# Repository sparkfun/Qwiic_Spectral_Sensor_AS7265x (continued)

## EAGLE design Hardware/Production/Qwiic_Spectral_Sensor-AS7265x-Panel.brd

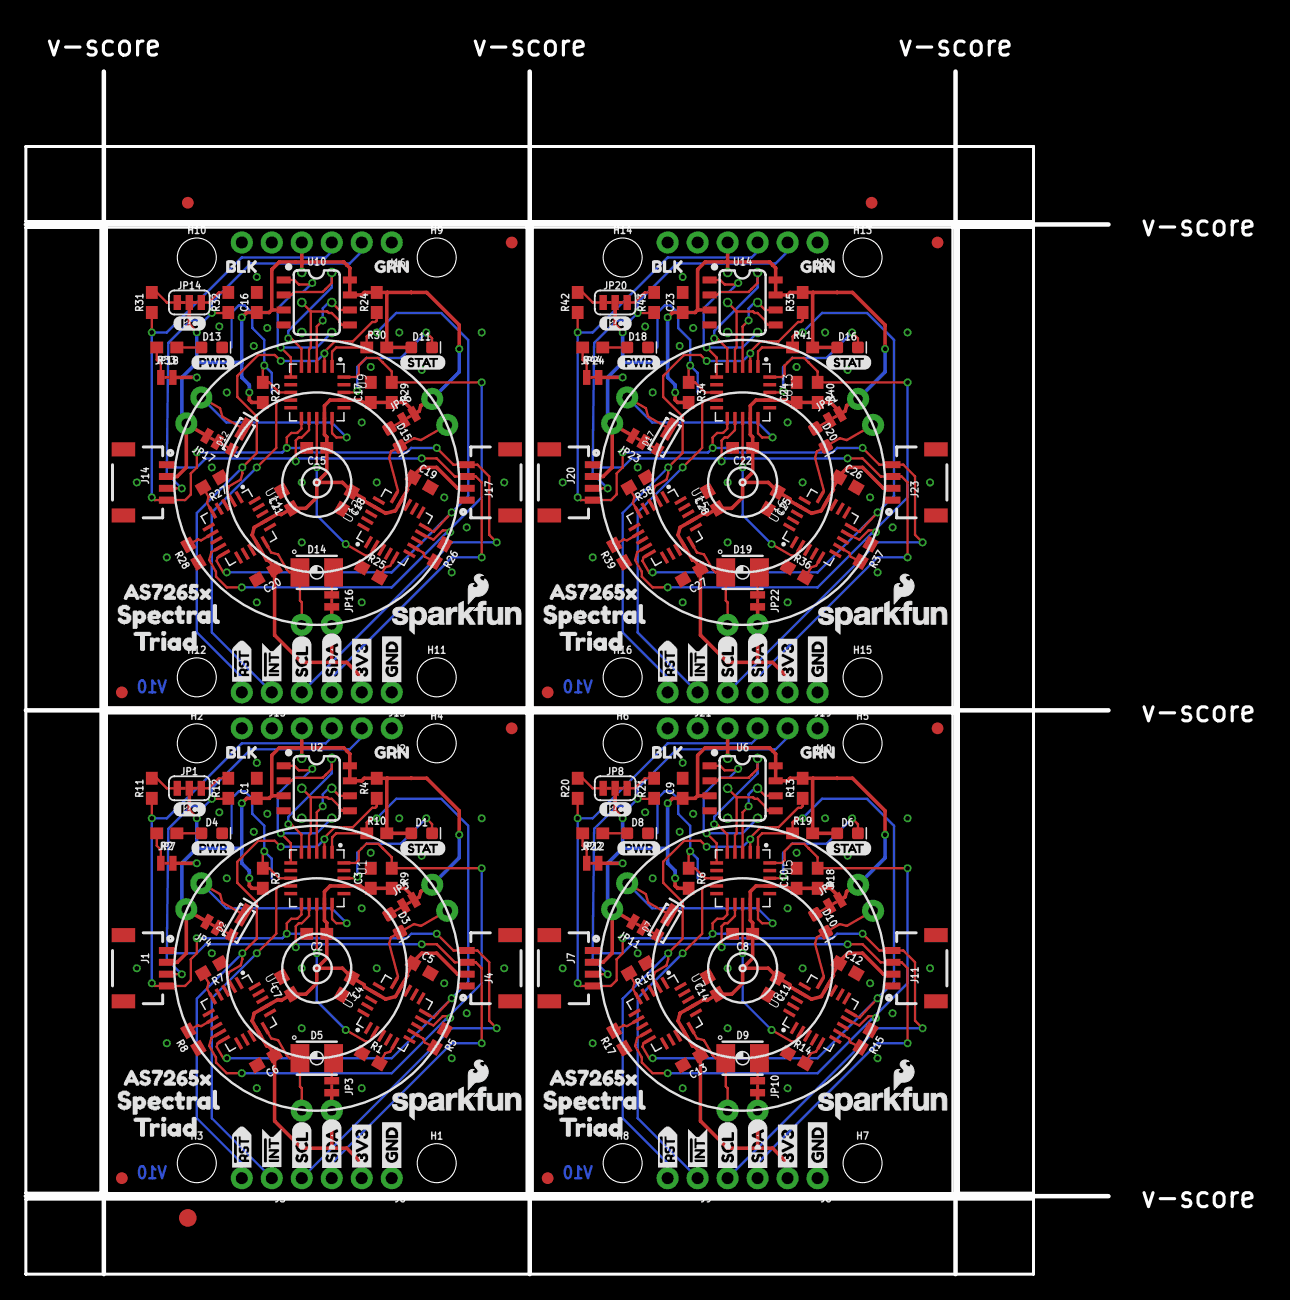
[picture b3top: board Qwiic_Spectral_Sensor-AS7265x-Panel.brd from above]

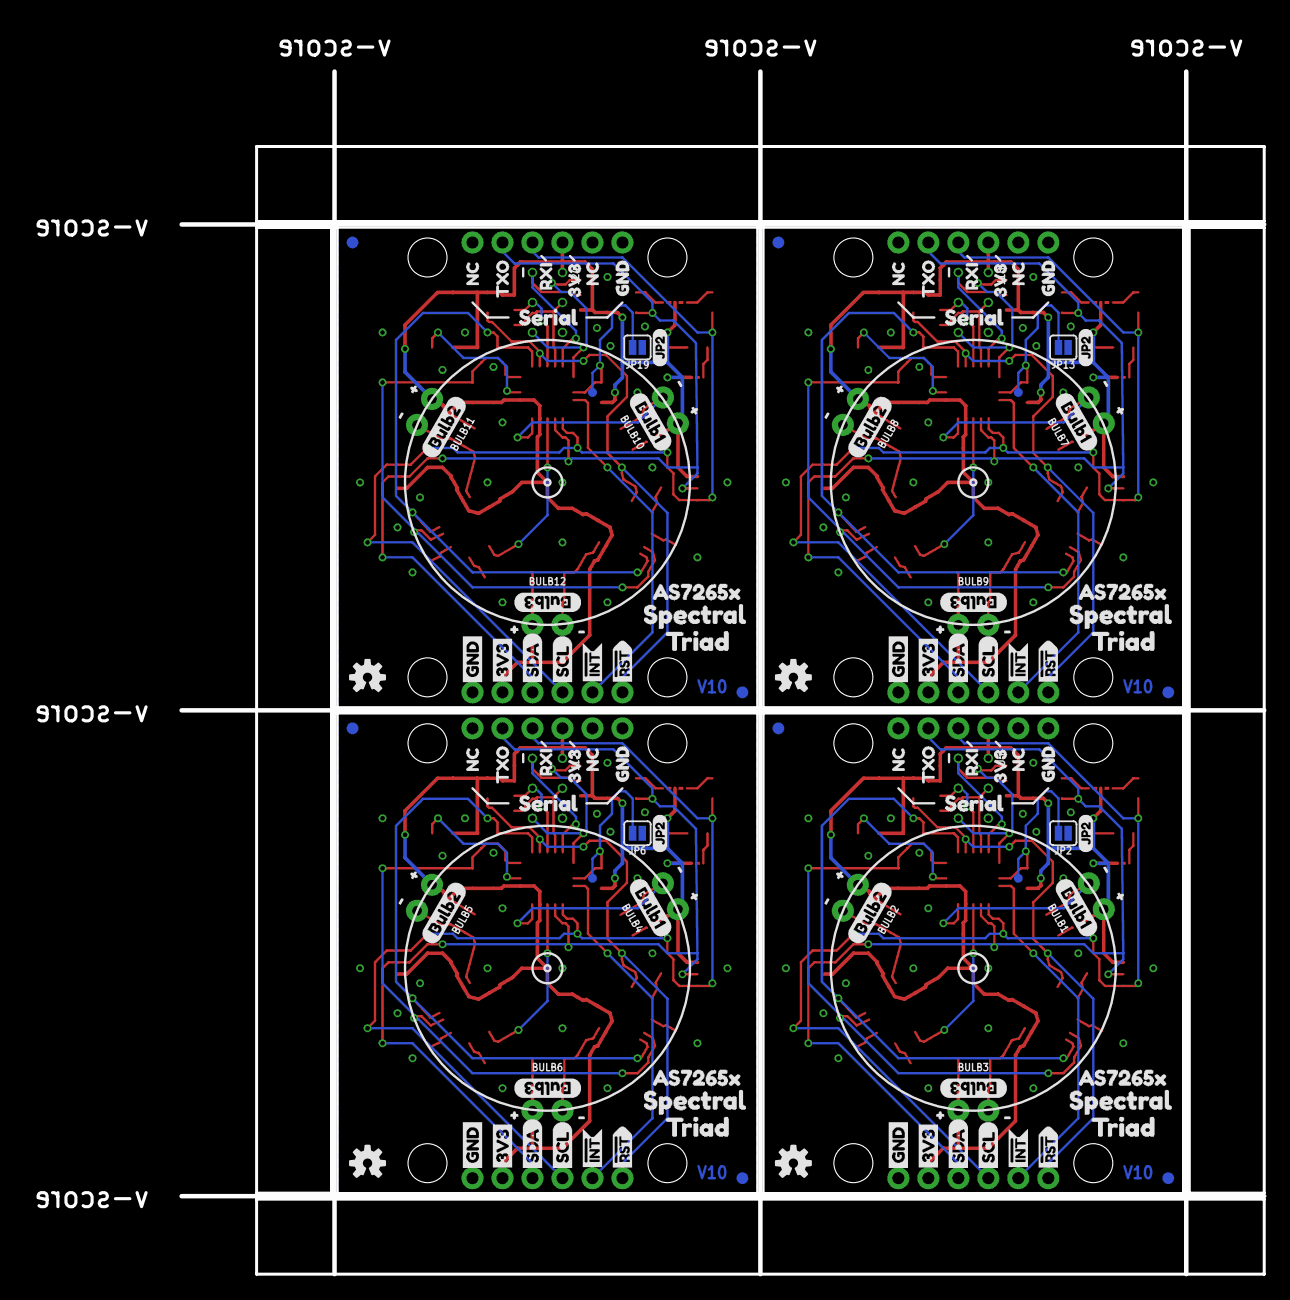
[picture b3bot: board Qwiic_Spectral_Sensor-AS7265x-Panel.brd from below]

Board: 2 copper layers, 104.9 x 105.7 mm, 375 parts (140 on the bottom side), 116 nets.

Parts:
BULB1, BULB2, BULB3, BULB4, BULB5, BULB6, BULB7, BULB8, BULB9, BULB10, BULB11, BULB12: LED_5MM_NOSILK
C1, C9, C16, C23: 1.0uF; 0603
C2, C4, C6, C8, C11, C13, C15, C18, C20, C22, C25, C27: 0.1uF; 0603
C3, C5, C7, C10, C12, C14, C17, C19, C21, C24, C26, C28: 10uF; 0603
D1, D6, D11, D16: BLUE; LED-0603
D2, D7, D12, D17: 5700k; SUPER_BRIGHT_SMD_LED_3014
D3, D10, D15, D20: IR; LED-0603
D4, D8, D13, D18: RED; LED-0603
D5, D9, D14, D19: UV; PLCC-2
E$1, E$2: FIDUCIAL-1X2
E$3: FIDUCIAL-1.5X3
FD1, FD2, FD3, FD4, FD5, FD6, FD7, FD8, FD9, FD10, FD11, FD12, FD13, FD14, FD15, FD16: FIDUCIAL1X2; FIDUCIAL-1X2
H1, H2, H3, H4, H5, H6, H7, H8, H9, H10, H11, H12, H13, H14, H15, H16: STAND-OFF
J1, J4, J7, J11, J14, J17, J20, J23: 1X04_1MM_RA
J2, J10, J16, J22: Serial Interface; 1X06_NO_SILK
J3, J9, J15, J21: 1X02_NO_SILK
J5, J12, J18, J24: Flash Programming; 2X3_TEST_POINTS
J6, J8, J13, J19: PTH; 1X04_NO_SILK
JP1, JP8, JP14, JP20: SMT-JUMPER_3_2-NC_TRACE_SILK
JP2, JP6, JP13, JP19: SMT-JUMPER_2_NO_SILK
JP3, JP4, JP5, JP7, JP9, JP10, JP11, JP12, JP15, JP16, JP17, JP18, JP21, JP22, JP23, JP24: SMT-JUMPER_2_NC_TRACE_NO-SILK
LOGO1, LOGO3, LOGO6, LOGO8: SFE_LOGO_NAME_FLAME.1_INCH; SFE_LOGO_NAME_FLAME_.1
LOGO2, LOGO4, LOGO5, LOGO7: OSHW-LOGOS; OSHW-LOGO-S
R1, R3, R4, R5, R6, R7, R8, R13, R14, R15, R16, R17, R23, R24, R25, R26, R27, R28, R34, R35, R36, R37, R38, R39: 10k; 0603
R2, R22, R33, R44: 1k; 0603
R9, R10, R11, R12, R18, R19, R20, R21, R29, R30, R31, R32, R40, R41, R42, R43: 2.2k; 0603
TP1, TP2, TP3, TP4: PAD.03X.03
U1, U5, U9, U13: AS72651; LGA20
U2, U6, U10, U14: 4MB Flash; SO08
U3, U8, U12, U16: AS72652; LGA20
U4, U7, U11, U15: AS72653; LGA20
U$1, U$36, U$37, U$75, U$76, U$77, U$115, U$116, U$117, U$155, U$156, U$157: #0
U$2, U$41, U$81, U$121: I_SUPER2_C-()-03
U$3, U$42, U$82, U$122: PWR-()-03
U$4, U$14, U$43, U$52, U$83, U$92, U$123, U$132: AS7265X0
U$5, U$44, U$84, U$124: BULB15
U$6, U$45, U$85, U$125: BULB26
U$7, U$46, U$86, U$126: BULB37
U$8, U$62, U$102, U$142: JP20
U$9, U$13, U$47, U$51, U$87, U$91, U$127, U$131: SPECTRAL1
U$10, U$48, U$88, U$128: STAT4
U$11, U$12, U$49, U$50, U$89, U$90, U$129, U$130: TRIAD2
U$15, U$53, U$93, U$133: 3V33
U$16, U$54, U$94, U$134: BLK7
U$17, U$55, U$95, U$135: GND5
U$18, U$56, U$96, U$136: GRN6
U$19, U$20, U$57, U$58, U$97, U$98, U$137, U$138: NC4
U$21, U$59, U$99, U$139: RXI2
U$22, U$60, U$100, U$140: SERIAL0
U$23, U$61, U$101, U$141: TXO1
U$24, U$31, U$63, U$70, U$103, U$110, U$143, U$150: 3V3-04
U$25, U$30, U$64, U$69, U$104, U$109, U$144, U$149: GND-04
U$26, U$32, U$65, U$71, U$105, U$111, U$145, U$151: SDA-[)
U$27, U$33, U$66, U$72, U$106, U$112, U$146, U$152: SCL-[)
U$28, U$34, U$67, U$73, U$107, U$113, U$147, U$153: INT#-[<-04
U$29, U$35, U$68, U$74, U$108, U$114, U$148, U$154: RST#-[>-04
U$38, U$39, U$40, U$78, U$79, U$80, U$118, U$119, U$120, U$158, U$159, U$160: #1

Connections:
3.3V: BULB1.A, BULB2.A, BULB3.A, C1.1, C2.1, C3.1, C4.1, C5.1, C6.1, C7.1, D1.A, J1.2, J2.4, J4.2, J5.2, J8.2, JP1.2, JP3.2, JP4.2, JP5.2, JP7.2, R3.2, R4.2, R9.2, R10.2, U1.14, U1.17, U2.3, U2.7, U2.8, U3.14, U3.17, U4.14, U4.17
3.3V1: BULB4.A, BULB5.A, BULB6.A, C8.1, C9.1, C10.1, C11.1, C12.1, C13.1, C14.1, D6.A, J6.2, J7.2, J10.4, J11.2, J12.2, JP8.2, JP9.2, JP10.2, JP11.2, JP12.2, R6.2, R13.2, R18.2, R19.2, U5.14, U5.17, U6.3, U6.7, U6.8, U7.14, U7.17, U8.14, U8.17
3.3V2: BULB7.A, BULB8.A, BULB9.A, C15.1, C16.1, C17.1, C18.1, C19.1, C20.1, C21.1, D11.A, J13.2, J14.2, J16.4, J17.2, J18.2, JP14.2, JP15.2, JP16.2, JP17.2, JP18.2, R23.2, R24.2, R29.2, R30.2, U9.14, U9.17, U10.3, U10.7, U10.8, U11.14, U11.17, U12.14, U12.17
3.3V3: BULB10.A, BULB11.A, BULB12.A, C22.1, C23.1, C24.1, C25.1, C26.1, C27.1, C28.1, D16.A, J19.2, J20.2, J22.4, J23.2, J24.2, JP20.2, JP21.2, JP22.2, JP23.2, JP24.2, R34.2, R35.2, R40.2, R41.2, U13.14, U13.17, U14.3, U14.7, U14.8, U15.14, U15.17, U16.14, U16.17
!CS_EE: J5.5, U1.6, U2.1
!CS_EE1: J12.5, U5.6, U6.1
!CS_EE2: J18.5, U9.6, U10.1
!CS_EE3: J24.5, U13.6, U14.1
!INT: J3.1, U1.9
!INT1: J9.1, U5.9
!INT2: J15.1, U9.9
!INT3: J21.1, U13.9
!RST: J3.2, R4.1, U1.2, U4.2
!RST1: J9.2, R13.1, U5.2, U7.2
!RST2: J15.2, R24.1, U9.2, U11.2
!RST3: J21.2, R35.1, U13.2, U15.2
!RST-ADDR: U1.13, U3.2
!RST-ADDR1: U5.13, U8.2
!RST-ADDR2: U9.13, U12.2
!RST-ADDR3: U13.13, U16.2
GND: C1.2, C2.2, C3.2, C4.2, C5.2, C6.2, C7.2, D4.C, J1.1, J2.6, J4.1, J5.6, J8.1, JP2.1, R1.1, R5.1, R7.1, R8.1, U1.16, U2.4, U3.16, U4.16
GND1: C8.2, C9.2, C10.2, C11.2, C12.2, C13.2, C14.2, D8.C, J6.1, J7.1, J10.6, J11.1, J12.6, JP6.1, R14.1, R15.1, R16.1, R17.1, U5.16, U6.4, U7.16, U8.16
GND2: C15.2, C16.2, C17.2, C18.2, C19.2, C20.2, C21.2, D13.C, J13.1, J14.1, J16.6, J17.1, J18.6, JP13.1, R25.1, R26.1, R27.1, R28.1, U9.16, U10.4, U11.16, U12.16
GND3: C22.2, C23.2, C24.2, C25.2, C26.2, C27.2, C28.2, D18.C, J19.1, J20.1, J22.6, J23.1, J24.6, JP19.1, R36.1, R37.1, R38.1, R39.1, U13.16, U14.4, U15.16, U16.16
I2C_ENB: JP2.2, R3.1, TP1.P$1, U1.8
I2C_ENB1: JP6.2, R6.1, TP2.P$1, U5.8
I2C_ENB2: JP13.2, R23.1, TP3.P$1, U9.8
I2C_ENB3: JP19.2, R34.1, TP4.P$1, U13.8
LED_DRV: BULB1.K, D2.C, U1.15
LED_DRV1: BULB2.K, D3.C, U3.15
LED_DRV2: BULB3.K, D5.C, U4.15
LED_DRV3: BULB4.K, D7.C, U5.15
LED_DRV4: BULB5.K, D10.C, U8.15
LED_DRV5: BULB6.K, D9.C, U7.15
LED_DRV6: BULB7.K, D12.C, U9.15
LED_DRV7: BULB8.K, D15.C, U12.15
LED_DRV8: BULB9.K, D14.C, U11.15
LED_DRV9: BULB10.K, D17.C, U13.15
LED_DRV10: BULB11.K, D20.C, U16.15
LED_DRV11: BULB12.K, D19.C, U15.15
MISO: J5.1, U1.5, U2.2
MISO1: J12.1, U5.5, U6.2
MISO2: J18.1, U9.5, U10.2
MISO3: J24.1, U13.5, U14.2
MOSI: J5.4, U1.4, U2.5
MOSI1: J12.4, U5.4, U6.5
MOSI2: J18.4, U9.4, U10.5
MOSI3: J24.4, U13.4, U14.5
unnamed: JP7.1, R2.2
unnamed: D1.C, U1.18
unnamed: R5.2, U3.7
unnamed: JP1.3, R12.2
unnamed: JP1.1, R11.2
unnamed: D2.A, JP4.1
unnamed: D4.A, R2.1
unnamed: D3.A, JP5.1
unnamed: R1.2, U3.5
unnamed: JP8.3, R21.2
unnamed: D5.A, JP3.1
unnamed: R8.2, U4.7
unnamed: R7.2, U4.5
unnamed: JP8.1, R20.2
unnamed: D6.C, U5.18
unnamed: D7.A, JP11.1
unnamed: D10.A, JP9.1
unnamed: R15.2, U8.7
unnamed: R14.2, U8.5
unnamed: D9.A, JP10.1
unnamed: R17.2, U7.7
unnamed: R16.2, U7.5
unnamed: JP12.1, R22.2
unnamed: D8.A, R22.1
unnamed: JP14.3, R32.2
unnamed: JP14.1, R31.2
unnamed: D11.C, U9.18
unnamed: D12.A, JP17.1
unnamed: D15.A, JP15.1
unnamed: R26.2, U12.7
unnamed: R25.2, U12.5
unnamed: D14.A, JP16.1
unnamed: R28.2, U11.7
unnamed: R27.2, U11.5
unnamed: JP18.1, R33.2
unnamed: D13.A, R33.1
unnamed: JP20.3, R43.2
unnamed: JP20.1, R42.2
unnamed: D16.C, U13.18
unnamed: D17.A, JP23.1
unnamed: D20.A, JP21.1
unnamed: R37.2, U16.7
unnamed: R36.2, U16.5
unnamed: D19.A, JP22.1
unnamed: R39.2, U15.7
unnamed: R38.2, U15.5
unnamed: JP24.1, R44.2
unnamed: D18.A, R44.1
RX/SCL: J1.4, J2.3, J4.4, J8.4, R11.1, U1.11
RX/SCL1: J6.4, J7.4, J10.3, J11.4, R20.1, U5.11
RX/SCL2: J13.4, J14.4, J16.3, J17.4, R31.1, U9.11
RX/SCL3: J19.4, J20.4, J22.3, J23.4, R42.1, U13.11
SCK: J5.3, U1.3, U2.6
SCK1: J12.3, U5.3, U6.6
SCK2: J18.3, U9.3, U10.6
SCK3: J24.3, U13.3, U14.6
SCL_S: R9.1, U1.20, U3.9, U4.9
SCL_S1: R18.1, U5.20, U7.9, U8.9
SCL_S2: R29.1, U9.20, U11.9, U12.9
SCL_S3: R40.1, U13.20, U15.9, U16.9
SDA_S: R10.1, U1.1, U3.10, U4.10
SDA_S1: R19.1, U5.1, U7.10, U8.10
SDA_S2: R30.1, U9.1, U11.10, U12.10
SDA_S3: R41.1, U13.1, U15.10, U16.10
TX/SDA: J1.3, J2.2, J4.3, J8.3, R12.1, U1.12
TX/SDA1: J6.3, J7.3, J10.2, J11.3, R21.1, U5.12
TX/SDA2: J13.3, J14.3, J16.2, J17.3, R32.1, U9.12
TX/SDA3: J19.3, J20.3, J22.2, J23.3, R43.1, U13.12

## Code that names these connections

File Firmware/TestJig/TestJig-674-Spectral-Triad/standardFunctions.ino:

/*
  Functions commonly used for jig testing but not unique to a given jig
*/

//We have to set any GPIO that is connected to the target to High Impedance
//Otherwise, the ATmega will parasitically power the target
void powerOffTarget()
{
  Serial.println("Powering off target");

  FJ.disableRegulator1();
  FJ.disableRegulator2();

  digitalWrite(SWITCH_ENABLE_SERIAL, LOW); //Disable
  digitalWrite(SWITCH_ENABLE_I2C, LOW); //Disable
  digitalWrite(SWITCH_ENABLE_SPI, LOW); //Disable

  //Go to high impedance for all I/O
  pinMode(TRIAD_INTERFACE_TYPE, INPUT);
  pinMode(TRIAD_INT, INPUT);
  pinMode(TRIAD_RST, INPUT);
  pinMode(TRIAD_EE_CS, INPUT);
  pinMode(MICROSD_CS, INPUT);

  //Turn off anything that may be providing power to target
  SD.end(); //Supported in Arduino 1.8.7
  SPI.end();
  Wire.end();
  Serial1.end();

  //Force I2C pins to inputs
  pinMode(18, INPUT);
  pinMode(19, INPUT);
  pinMode(20, INPUT);
  pinMode(21, INPUT);

  //Force SPI pins to inputs
  for (int x = 50 ; x < 60 ; x++)
  {
    digitalWrite(x, LOW);
    pinMode(x, INPUT);
  }
}

//This sets up the pins to various ins and outs
//This is external to setup so that we can call it after a powerOffTarget()
void initializeIO()
{
  //SPI.begin();
  //SPISettings(4000000, MSBFIRST, SPI_MODE0);

  pinMode(TRIAD_INTERFACE_TYPE, OUTPUT);
  digitalWrite(TRIAD_INTERFACE_TYPE, HIGH); //Set to I2C, not Serial
  pinMode(TRIAD_INT, INPUT);
  pinMode(TRIAD_RST, OUTPUT);
  digitalWrite(TRIAD_RST, HIGH); //Do not reset Triad
  pinMode(TRIAD_EE_CS, INPUT); //Go to high impedance for now

  setTestLEDs(STATUS_OFF);
}

//Power everything off
//Set fail LEDs
//Print a message letting user know what happened
void bailTest(String message)
{
  powerOffTarget();

  setTestLEDs(STATUS_MAINTEST_FAIL);

  Serial.println(message);
  Serial.println();
}

//Power everything off
//Set fail LEDs
//Print a message letting user know what happened
void bailPretest(String message)
{
  FJ.disableRegulator1();
  FJ.disableRegulator2();

  setTestLEDs(STATUS_PRETEST_FAIL);

  Serial.println(message);
  Serial.println();
}

//There's really only four states the LEDs could be in:
//Off
//Pretest Failed, both main LEDs off
//Pretest passed, main test fail
//Pretest passed, main test passed
void setTestLEDs(led_status state)
{
  if (state == STATUS_OFF)
  {
    digitalWrite(LED_PRETEST_PASS, LOW);
    digitalWrite(LED_PRETEST_FAIL, LOW);
    digitalWrite(LED_PASS, LOW);
    digitalWrite(LED_FAIL, LOW);
  }
  else if (state == STATUS_PRETEST_FAIL)
  {
    digitalWrite(LED_PRETEST_PASS, LOW);
    digitalWrite(LED_PRETEST_FAIL, HIGH);
    digitalWrite(LED_PASS, LOW);
    digitalWrite(LED_FAIL, LOW);
  }
  else if (state == STATUS_MAINTEST_FAIL)
  {
    digitalWrite(LED_PRETEST_PASS, HIGH);
    digitalWrite(LED_PRETEST_FAIL, LOW);
    digitalWrite(LED_PASS, LOW);
    digitalWrite(LED_FAIL, HIGH);
  }
  else if (state == STATUS_PASS)
  {
    digitalWrite(LED_PRETEST_PASS, HIGH);
    digitalWrite(LED_PRETEST_FAIL, LOW);
    digitalWrite(LED_PASS, HIGH);
    digitalWrite(LED_FAIL, LOW);
  }
}

//Turns on regulators and tests for shorts
//Returns success or fail
int powerUpAndTest()
{
  if (FJ.testRegulator1() == false)
  {
    Serial.println("Whoa! Short on power rail 1");
    return (fail);
  }

  if (FJ.testRegulator2() == false)
  {
    Serial.println("Whoa! Short on power rail 2");
    return (fail);
  }
  Serial.println("No shorts detected!");

  FJ.enableRegulator1();
  FJ.enableRegulator2();
  Serial.println("3.3V and 5V regulators powered up");
  return (success);
}

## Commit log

2018-10-15 Updating with Buzzard labels. Change logo to SparkFun. Change v to v10.
2018-10-15 Removing old files
2018-10-16 Adding prod_ids to new parts
2018-10-16 Moving board to origin
2018-10-16 Silk changes before panelization
2018-10-16 Adding LED disconnect jumpers
2018-10-16 Commit before panels
2018-10-19 Adding panel
2018-10-19 Adding Jig - It's called real jig to differentiate it from the Jig directory that is auto-generated a lot during jig testing.
2018-10-19 Removing unneeded pass-through holes
2018-10-25 Intermediate committ. Probably ignore the jig files.
2018-10-25 Adding readme
2018-10-25 Readme fix
2018-10-31 Adding test jig firmware
2018-11-01 Update to schematic table. Update to readme.
2018-11-08 Remvoing gerbers. Removing jig files. Rename datasheet. Clean up repo before post.
2019-03-29 Adding link to python program and thanks to section.
